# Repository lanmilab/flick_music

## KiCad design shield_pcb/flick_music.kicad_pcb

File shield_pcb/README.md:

# flick_music Arduino UNO R3 Shield

- Flick Large connects to J1 pin header or to bottom side FPC connector J2. It is not necessary to populate both.

- One audio output option is to solder J3 RCA, another 3.5mm jack connector J4.

- J5 is optional [PAM8302A](https://www.adafruit.com/product/2130) breakout header.

- JP1 jumper. Position 1: Flick large power from +5V(default); Position3: Flick Large power from Ard D10.

- JP2 jumper. Position 1: Amp enable pin(AMPSD) connected to +5V (default); Position3: Amp enable pin connected to Ard D7.

[LanmiLab](https://lanmilab.com/)

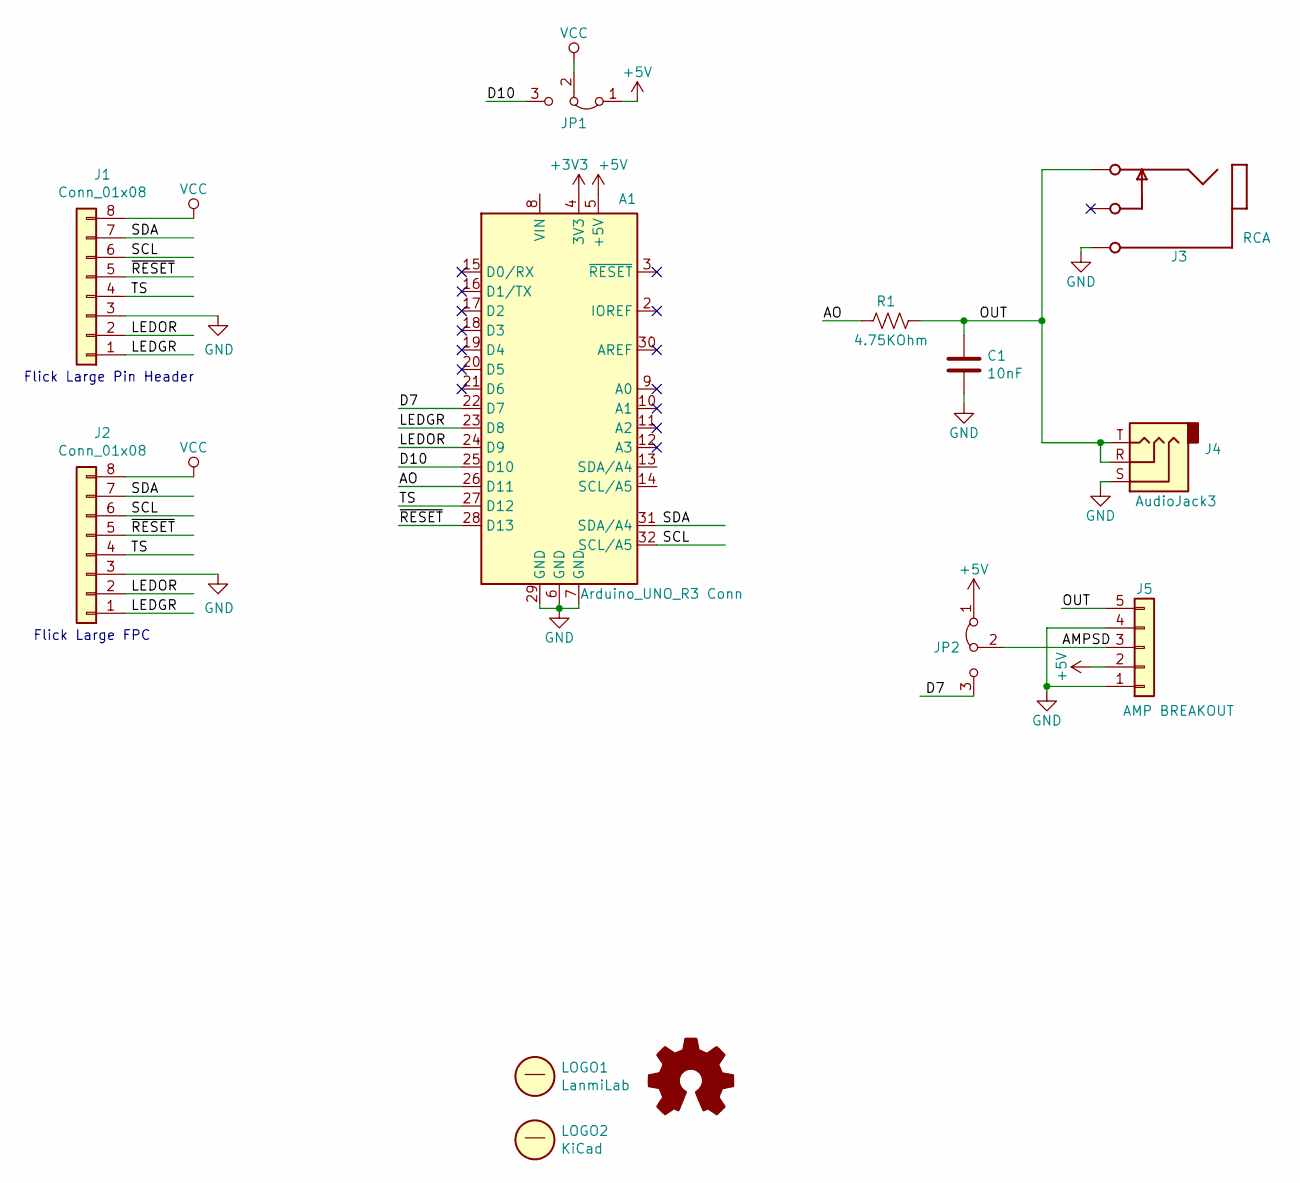
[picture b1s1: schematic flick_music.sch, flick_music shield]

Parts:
A1: Arduino_UNO_R3 Conn; Arduino_UNO_R3; Part Number M20-9994045
C1: 10nF; C_Disc_D3.8mm_W2.6mm_P2.50mm; Part Number C315C103K1R5TA
J1: Conn_01x08; PinHeader_1x08_P2.54mm_Horizontal; Part Number 68016-208HLF
J2: Conn_01x08; TE_0-1734839-8_1x08-1MP_P0.5mm_Horizontal; Part Number 0-1734839-8
J3: RCA; PJRAN1X1U01X; Part Number PJRAN1X1U01X
J4: AudioJack3; FC68131CLIFF; Part Number FC68131
J5: AMP BREAKOUT; PinSocket_1x05_P2.54mm_Vertical; Part Number PAM8302A Adafruit
JP1, JP2: Jumper_3_Bridged12; SolderJumper-3_P1.3mm_Bridged12_RoundedPad1.0x1.5mm_NumberL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
LOGO1: LanmiLab
LOGO2: KiCad; Logo_KiCad
LOGO3: Logo_Open_Hardware_Small; OSHW-Logo2_7.3x6mm_SilkScreen
R1: 4.75KOhm; R_Axial_DIN0207_L6.3mm_D2.5mm_P10.16mm_Horizontal; Part Number MCMF0W4FF4751A50

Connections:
+3V3: A1.4 (3V3)
+5V: A1.5 (+5V), J5.2, JP1.1 (A), JP2.1 (A)
/AMPSD: J5.3, JP2.2 (C)
/AO: A1.26 (D11), R1.2
/D7: A1.22 (D7), JP2.3 (B)
/D10: A1.25 (D10), JP1.3 (B)
/LEDGR: A1.23 (D8), J1.1, J2.1
/LEDOR: A1.24 (D9), J1.2, J2.2
/OUT: C1.1, J3.2, J4.R, J4.T, J5.5, R1.1
/SCL: A1.32 (SCL/A5), J1.6, J2.6
/SDA: A1.31 (SDA/A4), J1.7, J2.7
/TS: A1.27 (D12), J1.4, J2.4
/~RESET: A1.28 (D13), J1.5, J2.5
GND: A1.6 (GND), A1.7 (GND), A1.29 (GND), C1.2, J1.3, J2.3, J3.1, J4.S, J5.1, J5.4
VCC: J1.8, J2.8, JP1.2 (C)

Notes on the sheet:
Flick Large FPC
Flick Large Pin Header

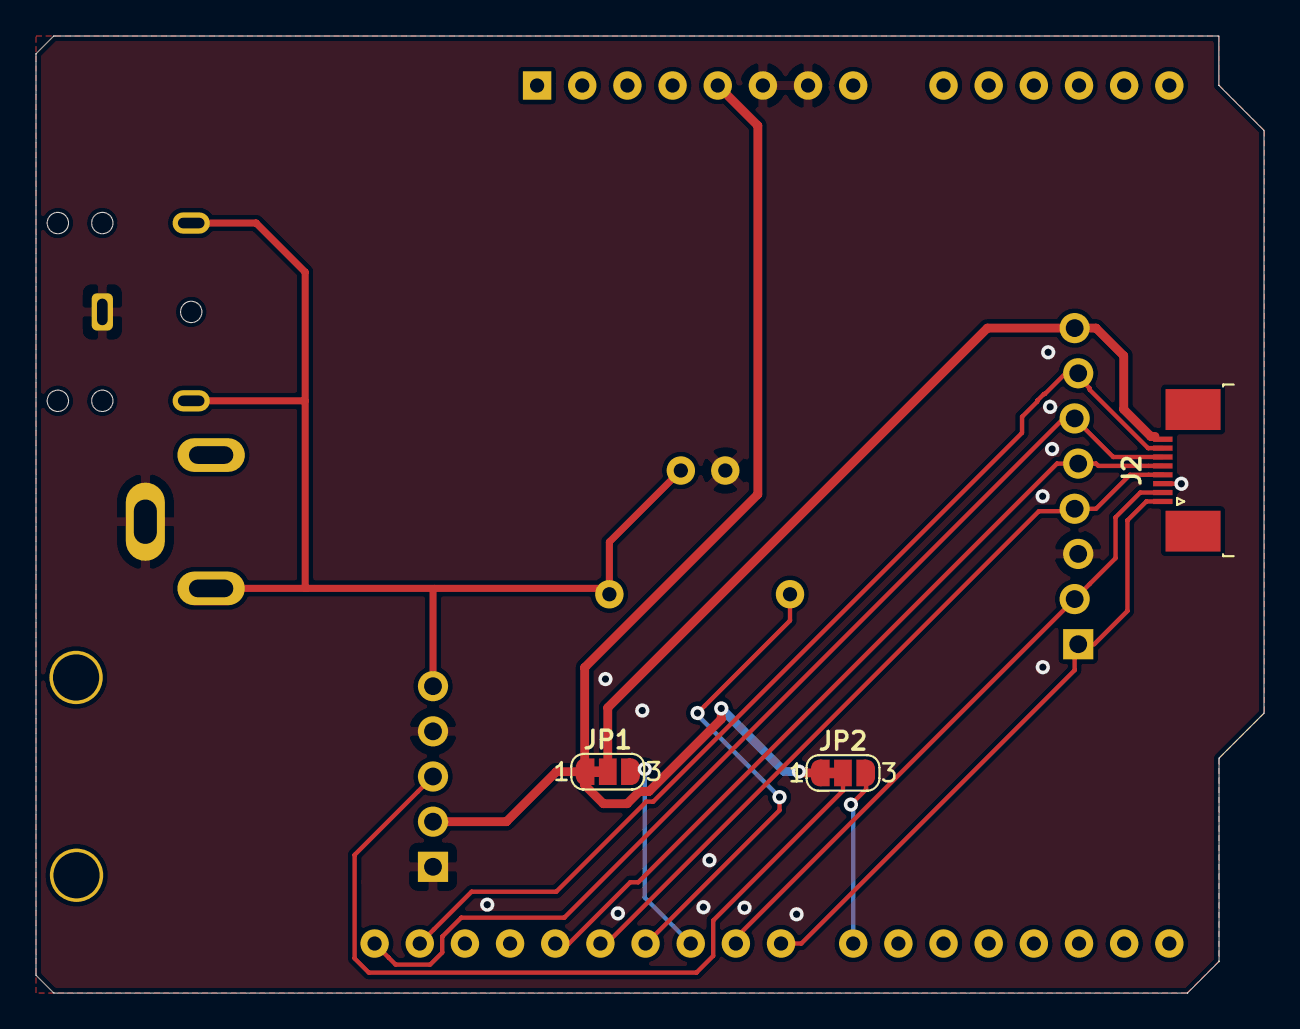
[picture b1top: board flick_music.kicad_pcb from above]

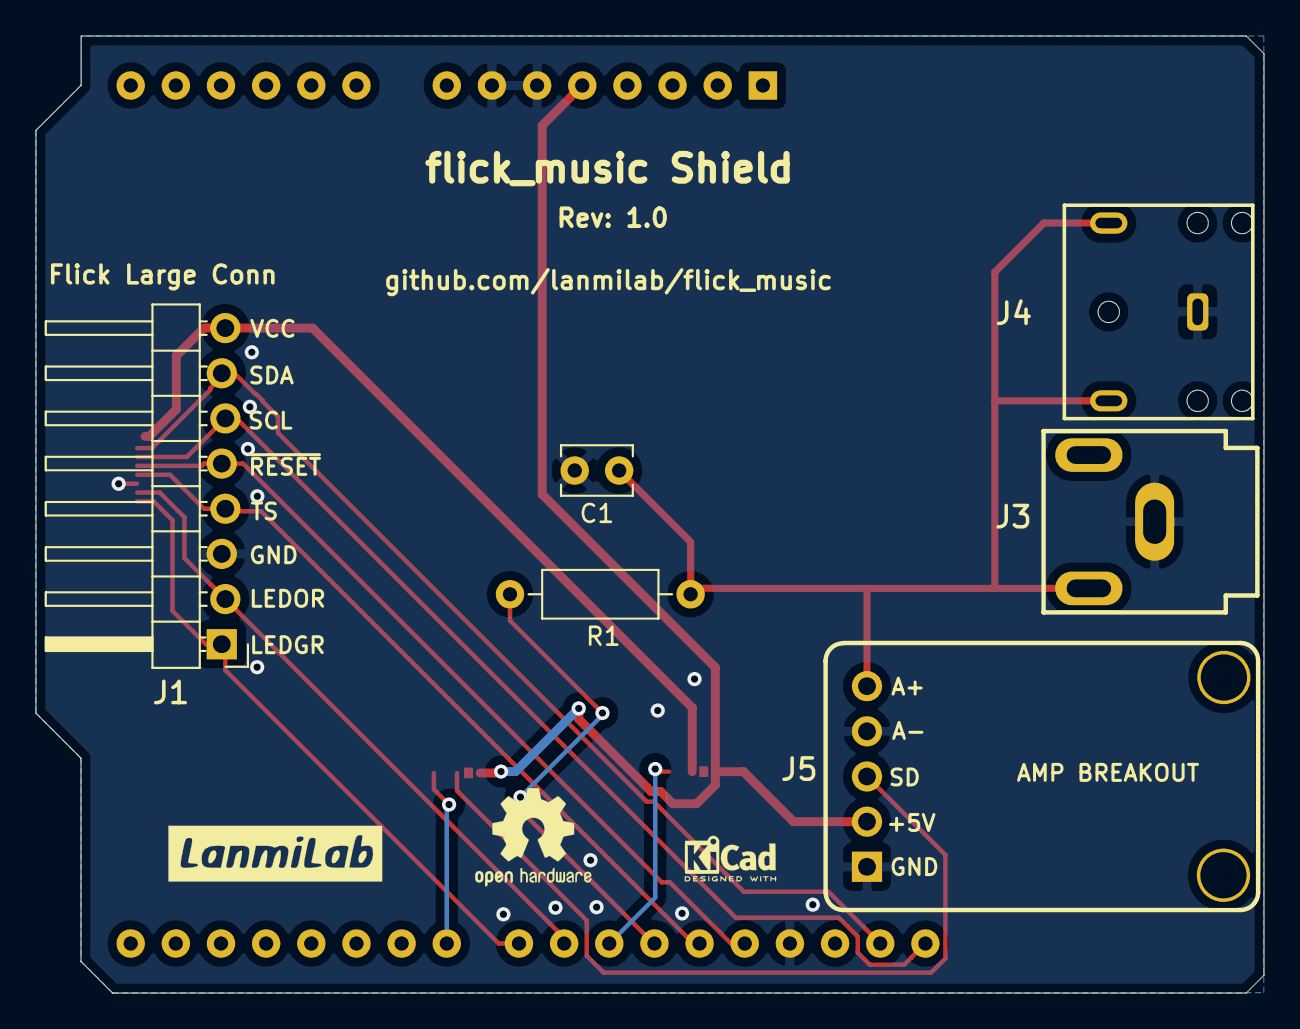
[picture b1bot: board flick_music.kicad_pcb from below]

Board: 2 copper layers, 69.1 x 53.8 mm, 13 parts (9 on the bottom side), 14 nets.

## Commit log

2021-01-29 Initial project
2021-10-25 Initial commit rev 1.0
